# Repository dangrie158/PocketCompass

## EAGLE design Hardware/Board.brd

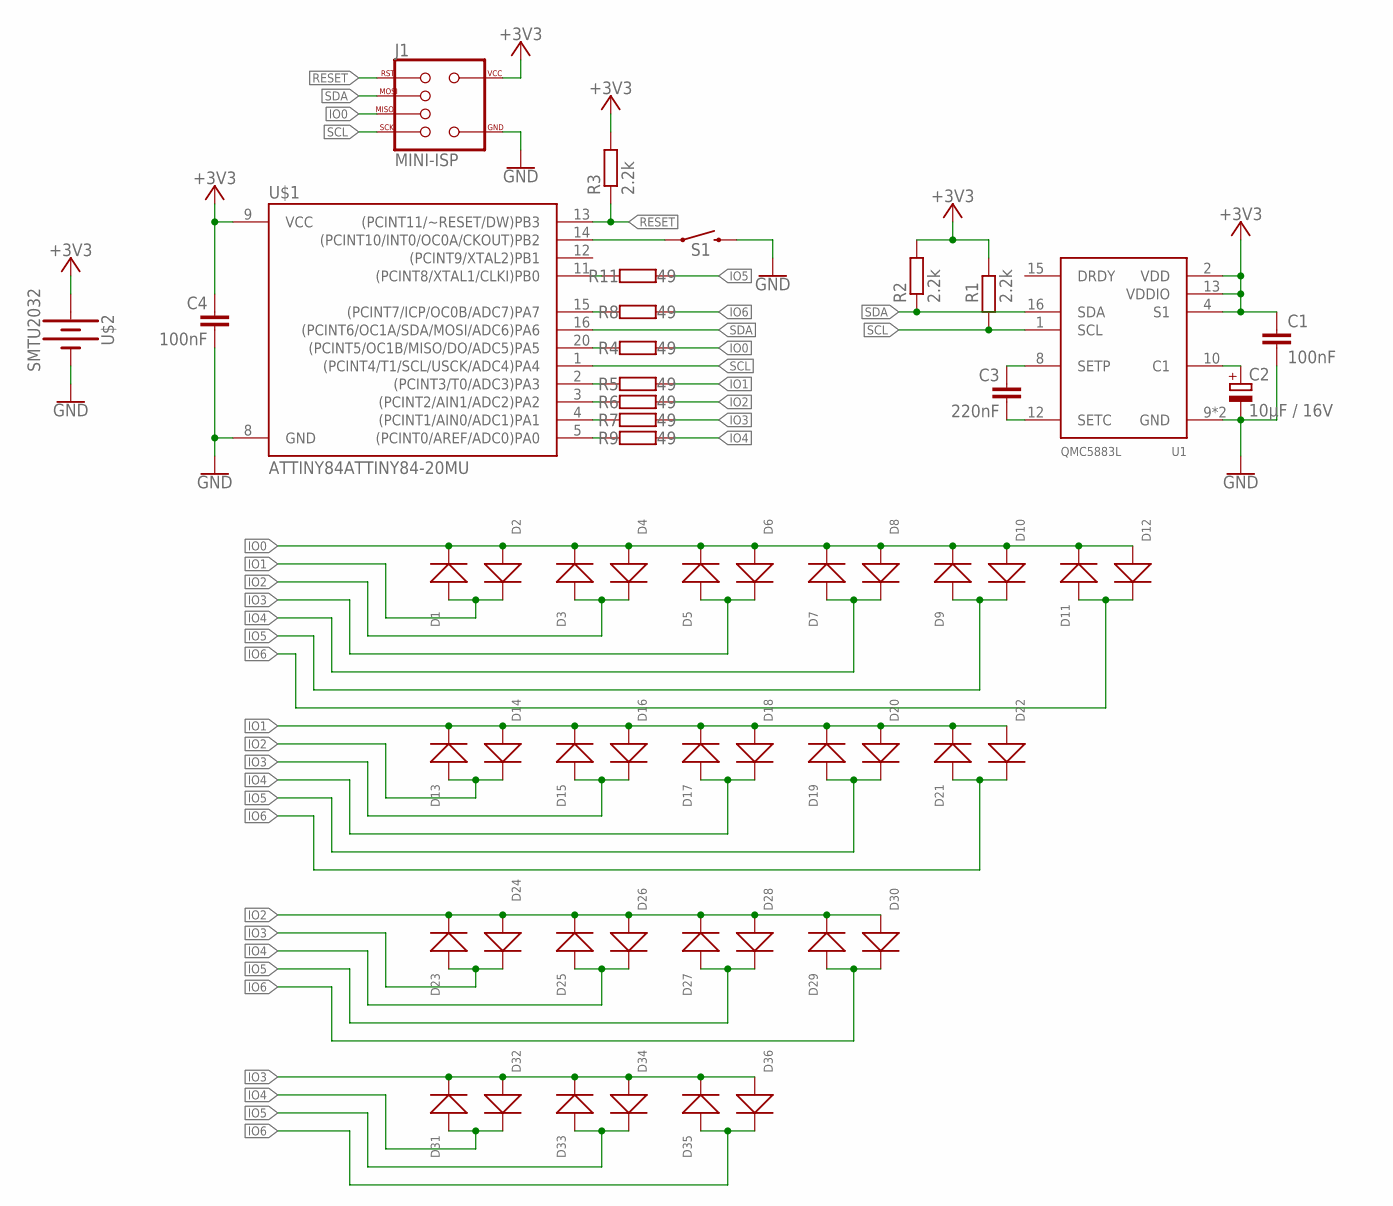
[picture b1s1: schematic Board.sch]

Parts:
C1, C4: 100nF; C0402K; JLC CL05B104KO5NNNC
C2: 10µF / 16V; CT3216; JLC TAJA106K016RNJ
C3: 220nF; C0402K; JLC CL05B224KO5NNNC
D1, D2, D3, D4, D5, D6, D7, D8, D10, D11, D12, D13, D14, D15, D16, D17, D19, D20, D21, D22, D23, D24, D25, D26, D28, D29, D30, D31, D32, D33, D34, D35: RED; SOD-523
D9, D18, D27, D36: YELLOW; SOD-523
J1: MINI-ISP
R1, R2, R3: 2.2k; R0402; JLC 0402WGF2201TCE
R4, R5, R6, R7, R8, R9, R11: 49; R0402; JLC 0603WAF470JT5E
S1: MOMENTARY-SWITCH-SPST-SMD-5.2MM; TACTILE_SWITCH_SMD_5.2MM; JLC TS-1187A-C-D-B
U1: QMC5883L; QFN50P300X300X102-16N; JLC QMC5883L-TR
U$1: ATTINY84ATTINY84-20MU; QFN20; JLC ATTINY44A-MU
U$2: SMTU2032

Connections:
+3V3: C1.1, C4.1, J1.VDD (2), R1.2, R2.2, R3.2, U1.2 (VDD), U1.4 (S1), U1.13 (VDDIO), U$1.9 (VCC), U$2.POS (+)
GND: C1.2, C2.-, C4.2, J1.GND (6), S1.3 (2), U1.9 (GND), U1.11 (GND), U$1.8 (GND), U$2.NEG (-)
IO0: D1.-, D2.+, D3.-, D4.+, D5.-, D6.+, D7.-, D8.+, D9.-, D10.+, D11.-, D12.+, J1.MISO (1), R4.1
IO1: D1.+, D2.-, D13.-, D14.+, D15.-, D16.+, D17.-, D18.+, D19.-, D20.+, D21.-, D22.+, R5.1
IO2: D3.+, D4.-, D13.+, D14.-, D23.-, D24.+, D25.-, D26.+, D27.-, D28.+, D29.-, D30.+, R6.1
IO3: D5.+, D6.-, D15.+, D16.-, D23.+, D24.-, D31.-, D32.+, D33.-, D34.+, D35.-, D36.+, R7.1
IO4: D7.+, D8.-, D17.+, D18.-, D25.+, D26.-, D31.+, D32.-, R9.1
IO5: D9.+, D10.-, D19.+, D20.-, D27.+, D28.-, D33.+, D34.-, R11.1
IO6: D11.+, D12.-, D21.+, D22.-, D29.+, D30.-, D35.+, D36.-, R8.1
unnamed: C2.+, U1.10 (C1)
unnamed: C3.1, U1.8 (SETP)
unnamed: C3.2, U1.12 (SETC)
unnamed: R11.2, U$1.11 ((PCINT8/XTAL1/CLKI)PB0)
unnamed: R8.2, U$1.15 ((PCINT7/ICP/OC0B/ADC7)PA7)
unnamed: R4.2, U$1.20 ((PCINT5/OC1B/MISO/DO/ADC5)PA5)
unnamed: S1.1, U$1.14 ((PCINT10/INT0/OC0A/CKOUT)PB2)
unnamed: R5.2, U$1.2 ((PCINT3/T0/ADC3)PA3)
unnamed: R6.2, U$1.3 ((PCINT2/AIN1/ADC2)PA2)
unnamed: R7.2, U$1.4 ((PCINT1/AIN0/ADC1)PA1)
unnamed: R9.2, U$1.5 ((PCINT0/AREF/ADC0)PA0)
RESET: J1.RESET (5), R3.1, U$1.13 ((PCINT11/~RESET/DW)PB3)
SCL: J1.SCK (3), R1.1, U1.1 (SCL), U$1.1 ((PCINT4/T1/SCL/USCK/ADC4)PA4)
SDA: J1.MOSI (4), R2.1, U1.16 (SDA), U$1.16 ((PCINT6/OC1A/SDA/MOSI/ADC6)PA6)

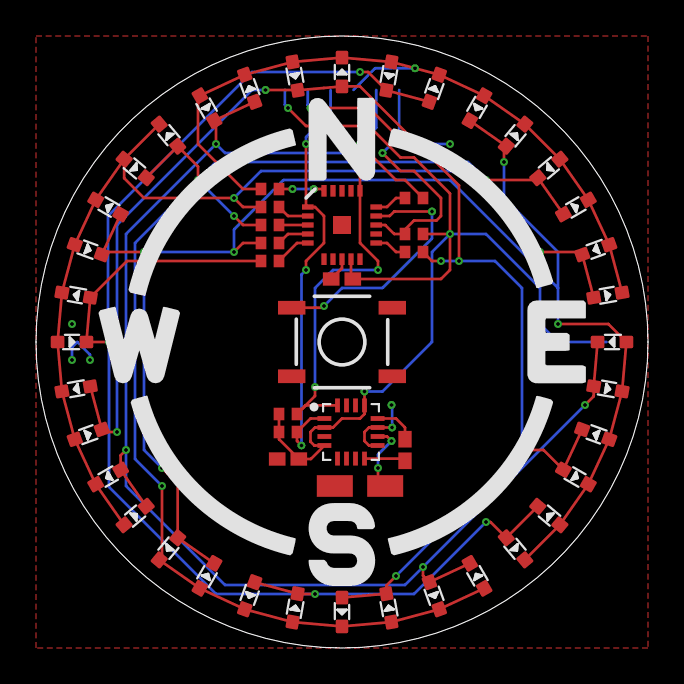
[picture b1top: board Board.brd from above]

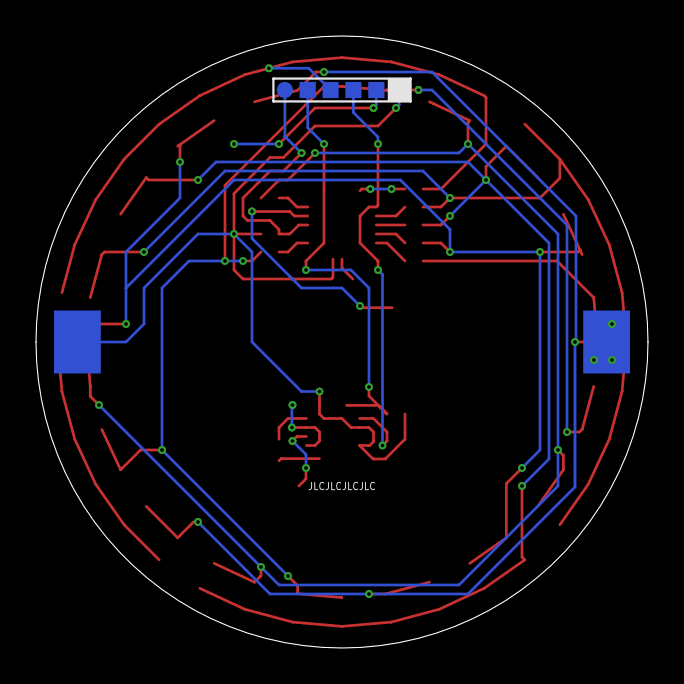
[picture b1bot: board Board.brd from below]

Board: 2 copper layers, 34.0 x 34.0 mm, 55 parts (2 on the bottom side), 23 nets.

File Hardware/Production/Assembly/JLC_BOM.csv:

"Comment","Designator","Footprint","LCSC Part"
"","S1","TACTILE_SWITCH_SMD_5.2MM","C318888"
"100nF","C1, C4","C0402K","C1525"
"10µF / 16V","C2","CT3216","C7171"
"2.2k","R1, R2, R3","R0402","C25879"
"220nF","C3","C0402K","C16772"
"49","R4, R5, R6, R7, R8, R9, R11","R0402","C23182"
"ATTINY84ATTINY84-20MU","U$1","QFN20","C123718"
"MINI-ISP","J1","MINI-ISP",""
"QMC5883L","U1","QFN50P300X300X102-16N","C192585"
"RED","D1, D2, D3, D4, D5, D6, D7, D8, D10, D11, D12, D13, D14, D15, D16, D17, D19, D20, D21, D22, D23, D24, D25, D26, D28, D29, D30, D31, D32, D33, D34, D35","SOD-523",""
"SMTU2032","U$2","SMTU2032",""
"YELLOW","D9, D18, D27, D36","SOD-523",""

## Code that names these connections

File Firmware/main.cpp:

#include <stdint.h>
#include <util/delay.h>
#include <avr/sleep.h>
#include <avr/interrupt.h>

#include "Wire.h"
#include "QMC5883L.h"

#define NUM_LEDS 36
#define NUM_LED_CHANS 7
#define ALL_OFF -1

QMC5883L compass;

const uint8_t highPins[NUM_LEDS] = {
	1, 0, 2, 0, 3, 0, 4, 0, 5, 0, 6, 0,
	2, 1, 3, 1, 4, 1, 5, 1, 6, 1,
	3, 2, 4, 2, 5, 2, 6, 2,
	4, 3, 5, 3, 6, 3};

const uint8_t lowPins[NUM_LEDS] = {
	0, 1, 0, 2, 0, 3, 0, 4, 0, 5, 0, 6,
	1, 2, 1, 3, 1, 4, 1, 5, 1, 6,
	2, 3, 2, 4, 2, 5, 2, 6,
	3, 4, 3, 5, 3, 6};

const uint8_t pinMapping[NUM_LED_CHANS] = {PA5, PA3, PA2, PA1, PA0, PB0, PA7};
volatile uint8_t *portMapping[NUM_LED_CHANS] = {&PORTA, &PORTA, &PORTA, &PORTA, &PORTA, &PORTB, &PORTA};
volatile uint8_t *ddrMapping[NUM_LED_CHANS] = {&DDRA, &DDRA, &DDRA, &DDRA, &DDRA, &DDRB, &DDRA};

volatile uint8_t *switchDDR = &DDRB;
volatile uint8_t *switchOR = &PORTB;
volatile uint8_t *switchIR = &PINB;
uint8_t switchPin = PB2;
uint8_t switchInt = INT0;

const uint8_t quarterLeds[4] = {8, 17, 26, 35};

void setLED(int8_t led)
{

	uint8_t highPin, lowPin;
	if (led == ALL_OFF)
	{
		highPin = NUM_LEDS + 1;
		lowPin = NUM_LEDS + 1;
	}
	else
	{
		highPin = highPins[led];
		lowPin = lowPins[led];
	}

	//Set all channels to High-Z Mode without Pullup
	for (uint8_t channel = 0; channel < NUM_LED_CHANS; channel++)
	{
		*(ddrMapping[channel]) &= ~(1 << pinMapping[channel]);
		*(portMapping[channel]) &= ~(1 << pinMapping[channel]);
	}
	// set the high pin as output driven high
	*(ddrMapping[highPin]) |= (1 << pinMapping[highPin]);
	*(portMapping[highPin]) |= (1 << pinMapping[highPin]);

	// set the low pin as output pulled low
	*(ddrMapping[lowPin]) |= (1 << pinMapping[lowPin]);
	*(portMapping[lowPin]) &= ~(1 << pinMapping[lowPin]);
}

void setup()
{
	//Input with pull-up enabled for switch input
	*switchDDR &= ~(1 << switchPin);
	*switchOR |= (1 << switchPin);

	// enable interrupts
	sei();

	Wire::init();

	compass.init();
	compass.setSamplingRate(50);
	compass.setRange(QMC5883L_CONFIG_8GAUSS);
}

ISR(INT0_vect)
{
	//do nothing, only to wakeup
}

void loop()
{
	if ((*switchIR & (1 << switchPin)))
	{
		setLED(ALL_OFF);
		//enable level triggered interrupt on INT0
		GIMSK |= (1 << INT0);
		set_sleep_mode(SLEEP_MODE_PWR_DOWN);
		sleep_mode();
	}

	// disable interrupt
	GIMSK &= ~(1 << INT0);

	for (uint8_t i = 0; i < 4; i++)
	{
		setLED(quarterLeds[i]);
		_delay_ms(1);
	}

	int heading = compass.readHeading();

	while (heading < 0)
	{
		heading += 360;
	}
	while (heading >= 360)
	{
		heading -= 360;
	}
	setLED((heading / 10) % 36);
	_delay_ms(3);
}

int main()
{
	setup();
	while (1)
	{
		loop();
	}
}

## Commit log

2019-11-06 initial Hardware commit
2019-11-07 added initial firmware version
2019-11-19 finished firmware functionality

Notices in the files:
parts and their libraries:
SparkFun-IC-Microcontroller: Licensing: Creative Commons ShareAlike 4.0 International - https://creativecommons.org/licenses/by-sa/4.0
